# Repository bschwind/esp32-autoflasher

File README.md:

# esp32-autoflasher

KiCad PCB based on the CP2102N USB-UART serial converter. This implements the "auto reset" circuits of most ESP32 dev boards. You can run things like esp-idf's `make flash` or flash code from the Arduino IDE without having to hold down any buttons.

Connect `EN`, `RX`, `TX`, `IO0`, and `GND` to their respective pins on the ESP32 (don't forget to swap the `RX` and `TX` pins!) and make sure you have the Silicon Labs CP210x driver installed on your OS.

You can order this PCB on [OshPark](https://oshpark.com/shared_projects/q04gDLKl)

## Required Parts

(All resistors and capacitors are size 1608 metric)

| Label | Description |
| --- | --- |
| U1 | CP2102N |
| R1 | 1 kOhm |
| R2 | 10 kOhm |
| R3 | 22.1 kOhm |
| R4 | 10 kOhm |
| R5 | 47.5 kOhm |
| C1 | 4.7 uF |
| C2 | 0.1 uF |
| C3 | 4.7 uF |
| C4 | 0.1 uF |
| Q1 | MMBT2222L transistor (SOT-23 package) |
| Q2 | MMBT2222L transistor (SOT-23 package) |

## Images

### Schematic

### PCB Layout

### Assembled

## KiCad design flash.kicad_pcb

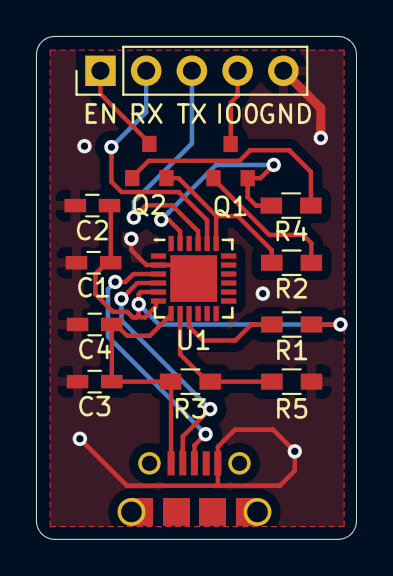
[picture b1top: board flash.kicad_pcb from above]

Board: 2 copper layers, 17.8 x 27.9 mm, 14 parts (0 on the bottom side), 15 nets.

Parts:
C1, C3: 4.7uF; C_0603_HandSoldering
C2, C4: 0.1uF; C_0603_HandSoldering
J1: USB_B_Micro; 10118194-0001lf-circle
J2: Conn_01x05; Pin_Header_Straight_1x05_Pitch2.54mm
Q1, Q2: MMBT2222ALT1G; mmbt2222alt1g
R1: 1 kΩ; R_0603_HandSoldering
R2, R4: 10 kΩ; R_0603_HandSoldering
R3: 22.1 kΩ; R_0603_HandSoldering
R5: 47.5 kΩ; R_0603_HandSoldering
U1: CP2102N-A01-GQFN24; QFN-24-1EP_4x4mm_Pitch0.5mm

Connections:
/DTR: Q1.2, R4.2, U1.23
/EN: J2.1, Q2.3
/GPIO0: J2.4, Q1.3
/RTS: Q2.2, R2.2, U1.19
/RX: J2.2, U1.20
/TX: J2.3, U1.21
GND: C1.2, C2.2, C3.2, C4.2, J1.5, J2.5, R5.2, U1.2, U1.25
unnamed: C1.1, C2.1, R1.1, U1.5, U1.6
unnamed: C3.1, C4.1, J1.1, R3.1, U1.7
unnamed: J1.2, U1.4
unnamed: J1.3, U1.3
unnamed: Q1.1, R2.1
unnamed: Q2.1, R4.1
unnamed: R1.2, U1.9
unnamed: R3.2, R5.1, U1.8

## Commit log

2019-05-06 Add schematic
2019-05-08 Add first iteration of PCB design
2019-05-11 Finish PCB
2019-06-08 Swap RX/TX pins, fix DTR/RTS transistor wiring
2019-06-08 Swap RX/TX silkscreen labels
2019-06-08 Adjust GND via from header pin
2019-10-18 Add board images and .gitignore
